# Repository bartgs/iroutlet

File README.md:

IrOutlet is an 8 port IR controlled power outlet.

A PIC16F15325 decodes the IR signal coming from a TSOP4836 IR receiver and steers a relay to switch on/off a power 
outlet port when an IR code is recognized.

IR codes:

1) Address: 0b00101 (Marantz)
2) Commands:
	- 0b00000000: switch all ports on
	- 0b00000001: switch port 1 on
	- 0b00000010: switch port 2 on
	- 0b00000011: switch port 3 on
	- 0b00000100: switch port 4 on
	- 0b00000101: switch port 5 on
	- 0b00000110: switch port 6 on
	- 0b00000111: switch port 7 on
	- 0b00001000: switch port 8 on
	- 0b00001001: switch all ports off
	- 0b00100000: switch port 1 off
	- 0b00100001: switch port 2 off
	- 0b00110010: switch port 3 off
	- 0b00110101: switch port 4 off
	- 0b00110100: switch port 5 off
	- 0b00110110: switch port 6 off
	- 0b00101001: switch port 7 off
	- 0b00111110: switch port 8 off

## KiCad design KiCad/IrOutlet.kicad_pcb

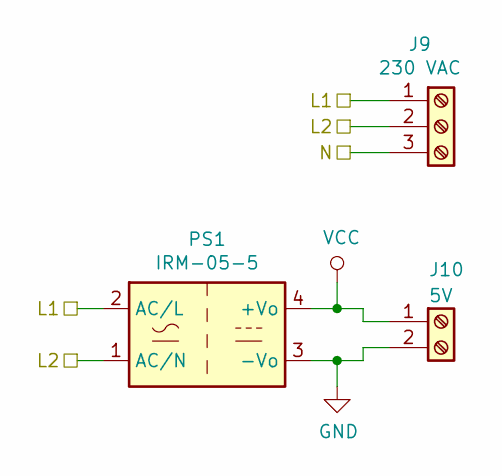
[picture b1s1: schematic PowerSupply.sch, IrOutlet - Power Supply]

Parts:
J9: 230 VAC; TB_1x3
J10: 5V; TB_1x2
PS1: IRM-05-5

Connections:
/PowerSupply/L1: J9.1, PS1.2 (AC/L); also elsewhere on the board
/PowerSupply/L2: J9.2, PS1.1 (AC/N); also elsewhere on the board
/PowerSupply/N: J9.3; also elsewhere on the board
GND: J10.2, PS1.3 (-Vo); also elsewhere on the board
VCC: J10.1, PS1.4 (+Vo); also elsewhere on the board

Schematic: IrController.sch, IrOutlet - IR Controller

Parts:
C1: 100nF; C_L7.62mm_W3.2mm
C2: 100uF; CAP_6.3mm_P2.50mm
D1: 1N5819; DIODE_H
J11: IrJack; HDR_1x3
J12: ICSP; HDR_1x5
R1: 100k; RES_H
U1: PIC16F15325; DIP-14

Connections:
/IrController/CLK: J12.5, U1.12
/IrController/DAT: J12.4, U1.13
/IrController/IR: J11.2, U1.11
/IrController/MCLR: J12.1, R1.2, U1.4
/RelaisDriver1.1/EN: U1.10; also elsewhere on the board
/RelaisDriver1.2/EN: U1.9; also elsewhere on the board
/RelaisDriver1.3/EN: U1.8; also elsewhere on the board
/RelaisDriver1.4/EN: U1.7; also elsewhere on the board
/RelaisDriver2.1/EN: U1.6; also elsewhere on the board
/RelaisDriver2.2/EN: U1.5; also elsewhere on the board
/RelaisDriver2.3/EN: U1.2; also elsewhere on the board
/RelaisDriver2.4/EN: U1.3; also elsewhere on the board
GND: C1.2, C2.2, J11.3, J12.3, U1.14; also elsewhere on the board
VCC: D1.2 (A), J11.1; also elsewhere on the board
VDD: C1.1, C2.1, D1.1 (K), J12.2, R1.1, U1.1

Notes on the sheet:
TSOP4836

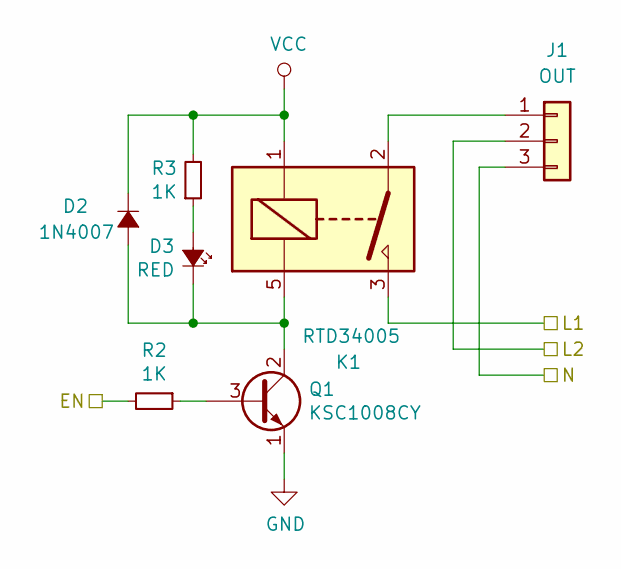
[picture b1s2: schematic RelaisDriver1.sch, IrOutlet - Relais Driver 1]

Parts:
D2: 1N4007; DIODE_H
D3: RED; HDR_1x2
J1: OUT; OUTLET
K1: RTD34005; RELAY_TE_RTD3405
Q1: KSC1008CY; TO-92
R2, R3: 1K; RES_H

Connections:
/PowerSupply/L1: K1.3; also elsewhere on the board
/PowerSupply/L2: J1.2; also elsewhere on the board
/PowerSupply/N: J1.3; also elsewhere on the board
/RelaisDriver1.1/EN: R2.2; also elsewhere on the board
GND: Q1.1 (E); also elsewhere on the board
unnamed: D2.2 (A), D3.1 (K), K1.5, Q1.2 (C)
unnamed: D3.2 (A), R3.1
unnamed: J1.1, K1.2
unnamed: Q1.3 (B), R2.1
VCC: D2.1 (K), K1.1, R3.2; also elsewhere on the board

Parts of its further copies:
D4, D6, D8: 1N4007; DIODE_H
D5, D7, D9: RED; HDR_1x2
J2, J3, J4: OUT; OUTLET
K2, K3, K4: RTD34005; RELAY_TE_RTD3405
Q2, Q3, Q4: KSC1008CY; TO-92
R4, R5, R6, R7, R8, R9: 1K; RES_H

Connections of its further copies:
/PowerSupply/L1: K2.3, K3.3, K4.3; also elsewhere on the board
/PowerSupply/L2: J2.2, J3.2, J4.2; also elsewhere on the board
/PowerSupply/N: J2.3, J3.3, J4.3; also elsewhere on the board
/RelaisDriver1.2/EN: R4.2; also elsewhere on the board
/RelaisDriver1.3/EN: R6.2; also elsewhere on the board
/RelaisDriver1.4/EN: R8.2; also elsewhere on the board
GND: Q2.1 (E), Q3.1 (E), Q4.1 (E); also elsewhere on the board
unnamed: D4.2 (A), D5.1 (K), K2.5, Q2.2 (C)
unnamed: D5.2 (A), R5.1
unnamed: D6.2 (A), D7.1 (K), K3.5, Q3.2 (C)
unnamed: D7.2 (A), R7.1
unnamed: D8.2 (A), D9.1 (K), K4.5, Q4.2 (C)
unnamed: D9.2 (A), R9.1
unnamed: J2.1, K2.2
unnamed: J3.1, K3.2
unnamed: J4.1, K4.2
unnamed: Q2.3 (B), R4.1
unnamed: Q3.3 (B), R6.1
unnamed: Q4.3 (B), R8.1
VCC: D4.1 (K), D6.1 (K), D8.1 (K), K2.1, K3.1, K4.1, R5.2, R7.2, R9.2; also elsewhere on the board

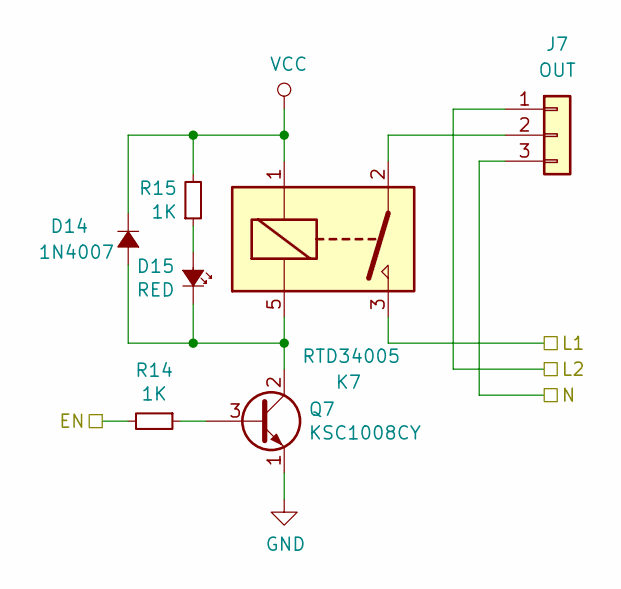
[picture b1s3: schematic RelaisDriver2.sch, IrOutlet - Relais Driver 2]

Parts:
D10: 1N4007; DIODE_H
D11: RED; HDR_1x2
J5: OUT; OUTLET
K5: RTD34005; RELAY_TE_RTD3405
Q5: KSC1008CY; TO-92
R10, R11: 1K; RES_H

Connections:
/PowerSupply/L1: K5.3; also elsewhere on the board
/PowerSupply/L2: J5.1; also elsewhere on the board
/PowerSupply/N: J5.3; also elsewhere on the board
/RelaisDriver2.1/EN: R10.2; also elsewhere on the board
GND: Q5.1 (E); also elsewhere on the board
unnamed: D10.2 (A), D11.1 (K), K5.5, Q5.2 (C)
unnamed: D11.2 (A), R11.1
unnamed: J5.2, K5.2
unnamed: Q5.3 (B), R10.1
VCC: D10.1 (K), K5.1, R11.2; also elsewhere on the board

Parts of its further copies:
D12, D14, D16: 1N4007; DIODE_H
D13, D15, D17: RED; HDR_1x2
J6, J7, J8: OUT; OUTLET
K6, K7, K8: RTD34005; RELAY_TE_RTD3405
Q6, Q7, Q8: KSC1008CY; TO-92
R12, R13, R14, R15, R16, R17: 1K; RES_H

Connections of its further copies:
/PowerSupply/L1: K6.3, K7.3, K8.3; also elsewhere on the board
/PowerSupply/L2: J6.1, J7.1, J8.1; also elsewhere on the board
/PowerSupply/N: J6.3, J7.3, J8.3; also elsewhere on the board
/RelaisDriver2.2/EN: R12.2; also elsewhere on the board
/RelaisDriver2.3/EN: R16.2; also elsewhere on the board
/RelaisDriver2.4/EN: R14.2; also elsewhere on the board
GND: Q6.1 (E), Q7.1 (E), Q8.1 (E); also elsewhere on the board
unnamed: D12.2 (A), D13.1 (K), K6.5, Q6.2 (C)
unnamed: D13.2 (A), R13.1
unnamed: D14.2 (A), D15.1 (K), K7.5, Q7.2 (C)
unnamed: D15.2 (A), R15.1
unnamed: D16.2 (A), D17.1 (K), K8.5, Q8.2 (C)
unnamed: D17.2 (A), R17.1
unnamed: J6.2, K6.2
unnamed: J7.2, K7.2
unnamed: J8.2, K8.2
unnamed: Q6.3 (B), R12.1
unnamed: Q7.3 (B), R14.1
unnamed: Q8.3 (B), R16.1
VCC: D12.1 (K), D14.1 (K), D16.1 (K), K6.1, K7.1, K8.1, R13.2, R15.2, R17.2; also elsewhere on the board

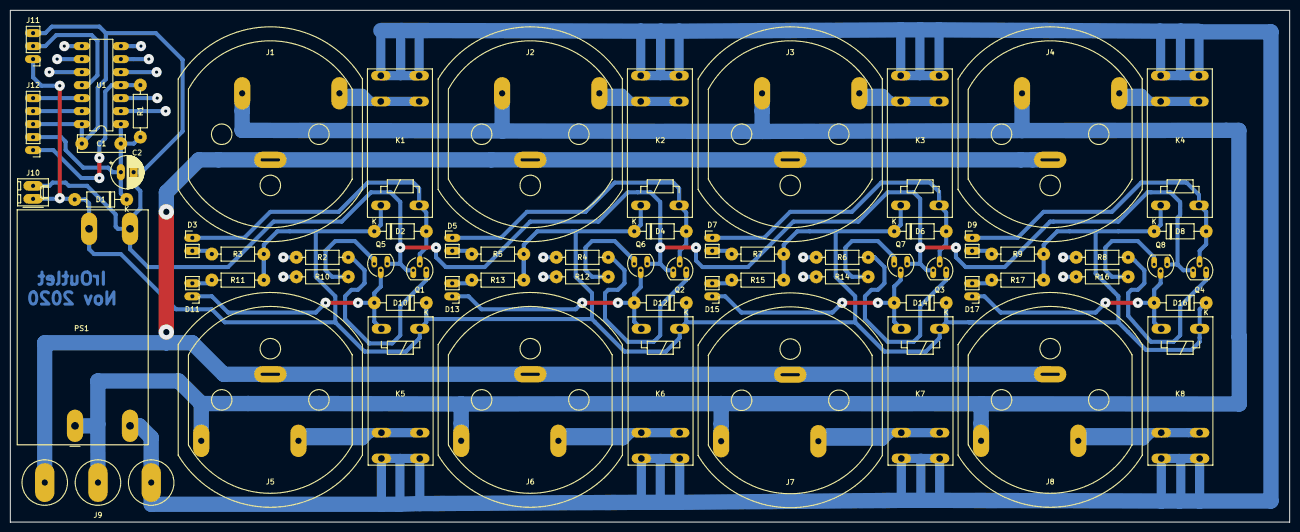
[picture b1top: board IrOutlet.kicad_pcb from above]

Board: 2 copper layers, 250.0 x 100.0 mm, 66 parts (0 on the bottom side), 50 nets.

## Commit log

2020-12-26 KiCad library cleanup
2020-12-26 Added KiCad footprints + fixed library references in schematic
2020-12-27 KiCad schematic: changed documentation links relative to project folder.
